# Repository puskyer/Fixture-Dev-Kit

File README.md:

# Fixture-Dev-Kit
A PCB for test fixture prototyping

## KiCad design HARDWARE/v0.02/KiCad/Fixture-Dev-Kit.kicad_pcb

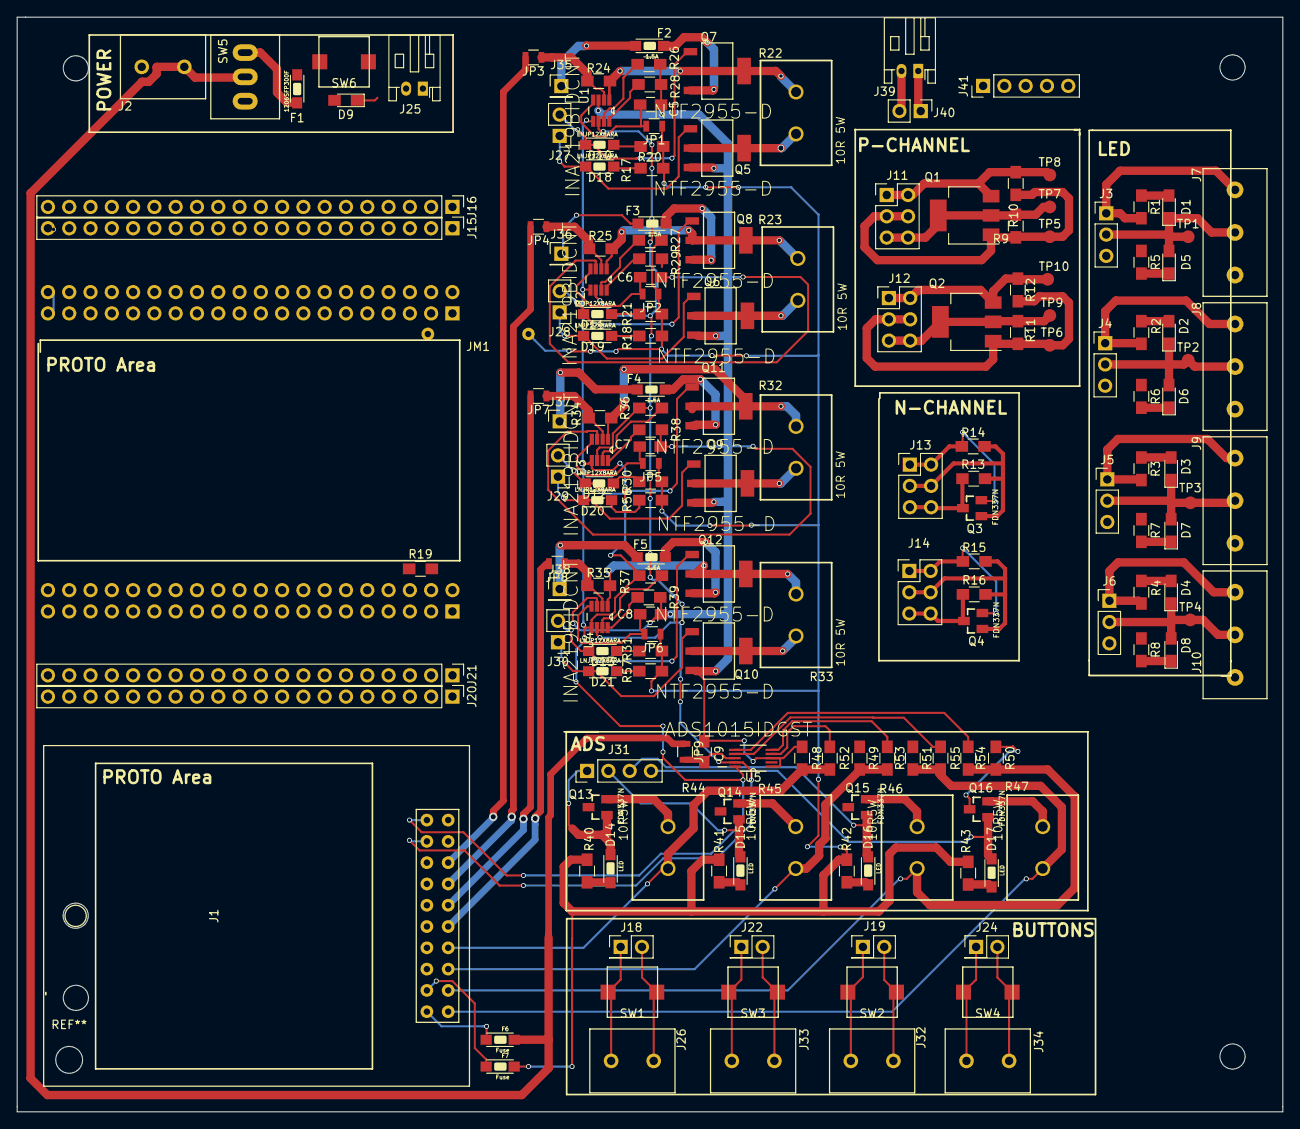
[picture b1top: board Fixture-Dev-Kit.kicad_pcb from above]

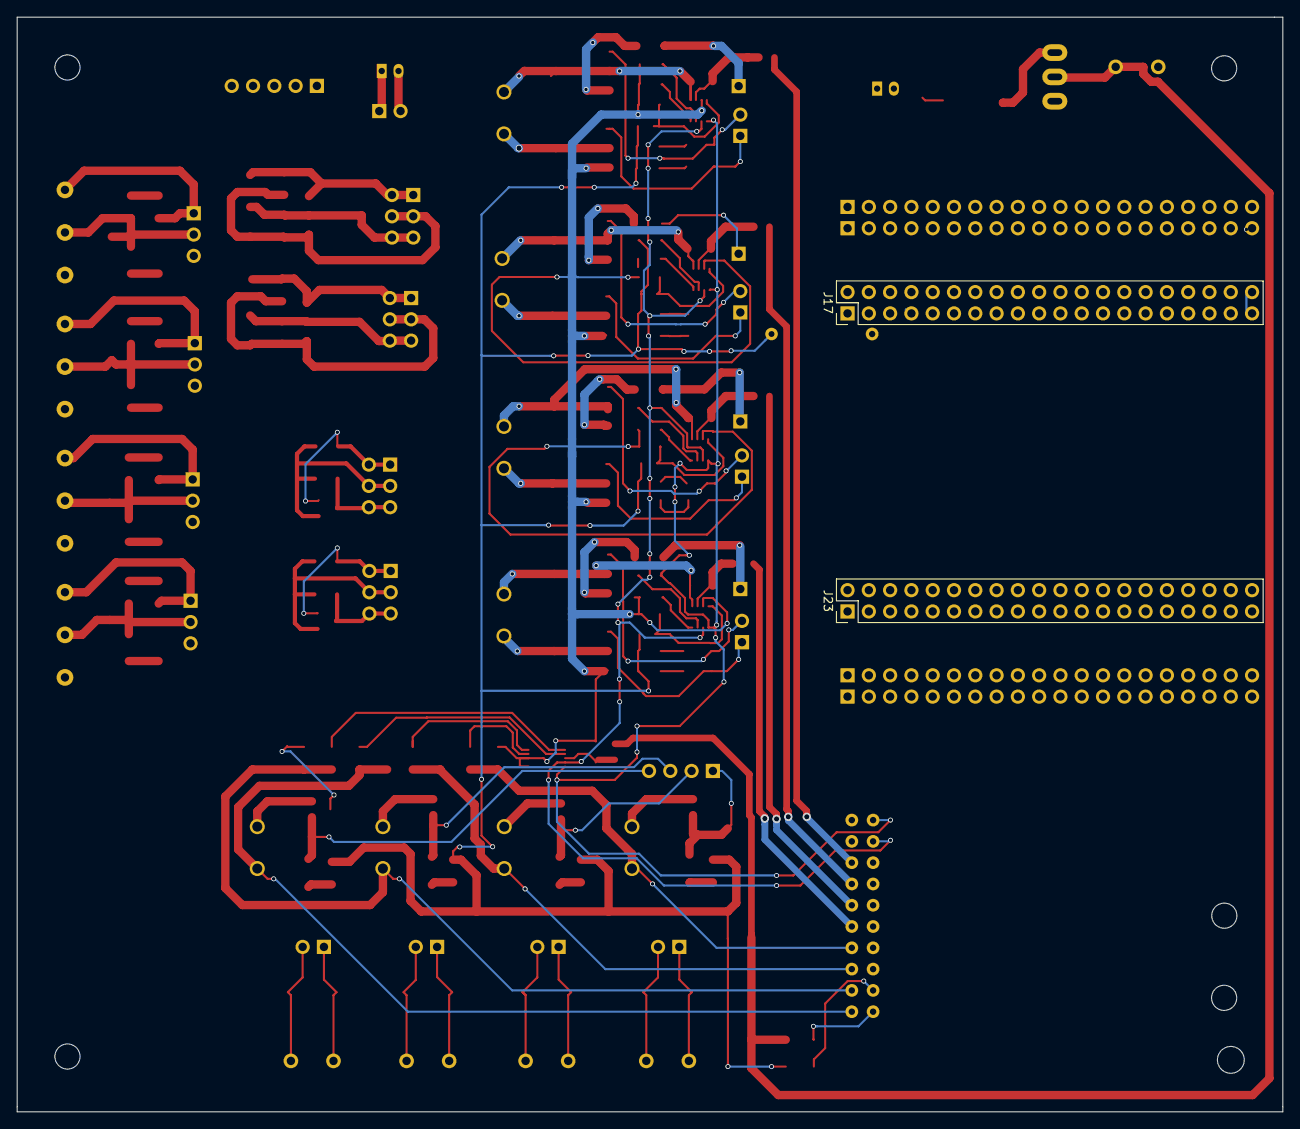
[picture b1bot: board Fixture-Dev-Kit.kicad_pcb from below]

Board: 2 copper layers, 151.0 x 130.6 mm, 178 parts (2 on the bottom side), 185 nets.

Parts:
C5, C6, C7, C8, C9: 0.1uF; C_0805_HandSoldering
D1, D2, D3, D4: Purple; LED_0805_HandSoldering
D5, D6, D7, D8: Green; LED_0805_HandSoldering
D9: LNJP12X8ARA; LED_0805_HandSoldering
D10, D11, D12, D13, D18, D19, D20, D21: LNJP12X8ARA; 1206
D14, D15, D16, D17: LED; 1206
F1: 1206SFP300F; 1206
F2, F3, F4, F5: 1.5A; 1206
F6, F7: Fuse; 1206
J1: DUT; DUT_HEADER_FOOTPRINT
J2: POWER; 2Pin5.08
J3: LED_0; Pin_Header_Straight_1x03_Pitch2.54mm
J4: LED_1; Pin_Header_Straight_1x03_Pitch2.54mm
J5: LED_2; Pin_Header_Straight_1x03_Pitch2.54mm
J6: LED_3; Pin_Header_Straight_1x03_Pitch2.54mm
J7: LED_0; 3Pin5.08
J8: LED_1; 3Pin5.08
J9: LED_2; 3Pin5.08
J10: LED_3; 3Pin5.08
J11, J12: FET_0; Pin_Header_Straight_2x03_Pitch2.54mm
J13: NFET_0; Pin_Header_Straight_2x03_Pitch2.54mm
J14: NFET_1; Pin_Header_Straight_2x03_Pitch2.54mm
J15, J16, J20, J21: Conn_01x20; Pin_Header_Straight_1x20_Pitch2.54mm
J17: CHIP4RH; Pin_Header_Straight_2x20_Pitch2.54mm
J18, J19, J22, J24: SW_0; Pin_Header_Straight_2x01_Pitch2.54mm
J23: CHIP4LH; Pin_Header_Straight_2x20_Pitch2.54mm
J25: JST-2P-RA; JST_PH_S2B-PH-K_02x2.00mm_Angled
J26, J32, J33, J34: SW_0; 2Pin5.08
J27, J28, J29, J30: INA_40; Pin_Header_Straight_1x02_Pitch2.54mm
J31: ADS; Pin_Header_Straight_1x04_Pitch2.54mm
J35: 40 V+; Pin_Header_Straight_1x01_Pitch2.54mm
J36: 41 V+; Pin_Header_Straight_1x01_Pitch2.54mm
J37: 42 V+; Pin_Header_Straight_1x01_Pitch2.54mm
J38: 43 V+; Pin_Header_Straight_1x01_Pitch2.54mm
J39: DUT BAT; JST_PH_S2B-PH-K_02x2.00mm_Angled
J40: DUT BAT; Pin_Header_Straight_1x02_Pitch2.54mm
J41: Conn_01x05; Pin_Header_Straight_1x05_Pitch2.54mm
JM1: JUMPER; Jumper
JP1, JP2, JP3, JP4, JP5, JP6, JP7, JP8, JP9: Jumper_NC_Small; R_0805
Q1, Q2: NTF2955T1G; SOT-223
Q3, Q4, Q13, Q14, Q15, Q16: FDN337N; SSOT-3
Q5, Q6, Q7, Q8, Q9, Q10, Q11, Q12: NTF2955-D; SOT230P700X180-4N
R1, R2, R3, R4, R5, R6, R7, R8, R26, R27, R28, R29, R36, R37, R38, R39: 1K; R_0805_HandSoldering
R9, R10, R11, R12, R13, R14, R15, R16: DNP; R_0805_HandSoldering
R17, R18, R20, R21, R30, R31, R40, R41, R42, R43, R56, R57: 160R; R_0805_HandSoldering
R19: 10K; R_0805_HandSoldering
R22, R23, R32, R33: 10R 5W; RES_TWM3J560E
R24, R25, R34, R35: 0.1R; R_0805_HandSoldering
R44, R45, R46, R47: 10R5W; RES_TWM3J560E
R48, R49, R50, R51: NC; R_0805_HandSoldering
R52: 0R; R_0805_HandSoldering
R53, R54, R55: 1R; R_0805_HandSoldering
SW1, SW2, SW3, SW4, SW6: TL9210AF260Q
SW5: YSS-19-1202-N
TP1, TP2, TP3, TP4: SIG; TestPoint
TP5: G0; TestPoint
TP6: G1; TestPoint
TP7, TP8, TP9, TP10: TEST; TestPoint
U1, U2, U3, U4: INA219BIDCNT; SOT65P280X145-8N
U5: ADS1015IDGST; SOP50P490X110-10N

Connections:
+5V: F6.1, J2.2, J41.1, J41.2, J41.3, J41.4, J41.5, JP9.1, SW5.2
/ADAPTER_ID: J1.16, J21.17, J23.34
/AIN0: J1.7, R44.2, R48.2, R52.1
/AIN1: J1.5, R45.2, R49.2, R53.1
/AIN2: J1.3, R46.2, R50.2, R54.1
/AIN3: J1.1, R47.2, R51.2, R55.1
/C4-VCC-3V3: F7.1, JM1.1, JP1.1, JP2.1, JP5.1, JP6.1, R17.2, R18.2, R20.2, R21.2, R27.2, R30.2, R31.2, R40.2, R41.2, R42.2, R43.2, R56.2, R57.2
/Fixture Dev Kit - ADS/AIN0_XIO: D14.1, J31.1, Q13.1
/Fixture Dev Kit - ADS/AIN1_XIO: D15.1, J31.2, Q14.1
/Fixture Dev Kit - ADS/AIN2_XIO: D16.1, J31.3, Q15.1
/Fixture Dev Kit - ADS/AIN3_XIO: D17.1, J31.4, Q16.1
/Fixture Dev Kit - Functional Computer/BAT: J21.4, J23.8, J25.2
/Fixture Dev Kit - Functional Computer/C4-PWR-IN: F1.2, J21.1, J23.2
/Fixture Dev Kit - Functional Computer/I2C-SCK: J15.19, J17.37
/Fixture Dev Kit - Functional Computer/I2C-SDA: J15.18, J17.35
/Fixture Dev Kit - Functional Computer/LOLN: J16.3, J17.6
/Fixture Dev Kit - Functional Computer/LOLP: J16.2, J17.4
/Fixture Dev Kit - Functional Computer/LORN: J16.5, J17.10
/Fixture Dev Kit - Functional Computer/LORP: J16.4, J17.8
/Fixture Dev Kit - Functional Computer/PWRON: J21.5, J23.10, SW6.1
/Fixture Dev Kit - Functional Computer/STATUSLED: D9.2, J15.5, J17.9, JM1.2
/Fixture Dev Kit - Functional Computer/TS: J21.3, J23.6, R19.1
/Fixture Dev Kit - INA/INA40_XIO: D10.1, J27.2, Q7.1
/Fixture Dev Kit - INA/INA41_XIO: D11.1, J28.2, Q8.1
/Fixture Dev Kit - INA/INA42_XIO: D12.1, J29.2, Q11.1
/Fixture Dev Kit - INA/INA43_XIO: D13.1, J30.2, Q12.1
/Fixture Dev Kit - INA/LOAD40_XIO: D18.1, J27.1, Q5.1
/Fixture Dev Kit - INA/LOAD41_XIO: D19.1, J28.1, Q6.1
/Fixture Dev Kit - INA/LOAD42_XIO: D20.1, J29.1, Q9.1
/Fixture Dev Kit - INA/LOAD43_XIO: D21.1, J30.1, Q10.1
/Fixture Dev Kit - PMosfets/Drain0: J11.5, J11.6, Q1.2, Q1.4, R9.2, TP7.1
/Fixture Dev Kit - PMosfets/Drain1: J12.5, J12.6, Q2.2, Q2.4, R11.2, TP9.1
/Fixture Dev Kit - PMosfets/Gate0: J11.3, J11.4, Q1.1, R9.1, R10.2, TP5.1
/Fixture Dev Kit - PMosfets/Gate1: J12.3, J12.4, Q2.1, R11.1, R12.2, TP6.1
/Fixture Dev Kit - PMosfets/Source0: J11.1, J11.2, Q1.3, R10.1, TP8.1
/Fixture Dev Kit - PMosfets/Source1: J12.1, J12.2, Q2.3, R12.1, TP10.1
/Fixture Dev Kits - NMosfets/Drain_0: J13.5, J13.6, Q3.3, R14.1
/Fixture Dev Kits - NMosfets/Drain_1: J14.5, J14.6, Q4.3, R16.1
/Fixture Dev Kits - NMosfets/Gate_0: J13.3, J13.4, Q3.1, R13.1, R14.2
/Fixture Dev Kits - NMosfets/Gate_1: J14.3, J14.4, Q4.1, R15.1, R16.2
/Fixture Dev Kits - NMosfets/Source_0: J13.1, J13.2, Q3.2, R13.2
/Fixture Dev Kits - NMosfets/Source_1: J14.1, J14.2, Q4.2, R15.2
/I2C-SCK: J1.20, R37.2, U1.5, U2.5, U3.5, U4.5, U5.10
/I2C-SDA: J1.18, R36.2, U1.6, U2.6, U3.6, U4.6, U5.9
/INA40_V-: J1.15, JP3.2
/INA41_V-: J1.13, JP4.2
/INA42_V-: J1.11, JP7.2
/INA43_V-: J1.9, JP8.2
/UART-RX: J1.17, J15.3, J17.5
/UART-TX: J1.19, J15.2, J17.3
GND: C5.1, C6.1, C7.1, C8.1, C9.2, D9.1, J1.6, J1.8, J1.10, J1.12, J1.14, J2.1, J3.3, J4.3, J5.3, J6.3, J7.3, J8.3, J9.3, J10.3, J15.1, J15.13, J15.20, J16.6, J16.20, J17.1, J17.25, J17.39, J17.40, J20.1, J20.7, J20.19, J20.20, J21.2, J21.6, J21.19, J21.20, J23.1, J23.4, J23.12, J23.13, J23.37, J23.38, J23.39, J23.40, J25.1, Q5.3, Q6.3, Q9.3, Q10.3, Q13.3, Q14.3, Q15.3, Q16.3, R5.1, R6.1, R7.1, R8.1, R19.2, R26.2, R28.2, R29.2, R38.2, R39.2, R48.1, R49.1, R50.1, R51.1, SW6.2, U1.3, U2.3, U3.3, U4.3, U5.1, U5.3
unnamed: C5.2, JP1.2, U1.4
unnamed: C6.2, JP2.2, U2.4
unnamed: C7.2, JP5.2, U3.4
unnamed: C8.2, JP6.2, U4.4
unnamed: C9.1, JP9.2, U5.8
unnamed: D1.1, D5.2, J3.2, J7.2, TP1.1
unnamed: D1.2, R1.1
unnamed: D2.1, D6.2, J4.2, J8.2, TP2.1
unnamed: D2.2, R2.1
unnamed: D3.1, D7.2, J5.2, J9.2, TP3.1
unnamed: D3.2, R3.1
unnamed: D4.1, D8.2, J6.2, J10.2, TP4.1
unnamed: D4.2, R4.1
unnamed: D5.1, R5.2
unnamed: D6.1, R6.2
unnamed: D7.1, R7.2
unnamed: D8.1, R8.2
unnamed: D10.2, R20.1
unnamed: D11.2, R21.1
unnamed: D12.2, R30.1
unnamed: D13.2, R31.1
unnamed: D14.2, R40.1
unnamed: D15.2, R41.1
unnamed: D16.2, R42.1
unnamed: D17.2, R43.1
unnamed: D18.2, R17.1
unnamed: D19.2, R18.1
unnamed: D20.2, R56.1
unnamed: D21.2, R57.1
unnamed: F1.1, SW5.3
unnamed: F2.1, Q7.3
unnamed: F2.2, J35.1
unnamed: F3.1, Q8.3
unnamed: F3.2, J36.1
unnamed: F4.1, Q11.3
unnamed: F4.2, J37.1
unnamed: F5.1, Q12.3
unnamed: F5.2, J38.1
unnamed: F6.2, J1.2
unnamed: F7.2, J1.4
unnamed: J3.1, J7.1, R1.2
unnamed: J4.1, J8.1, R2.2
unnamed: J5.1, J9.1, R3.2
unnamed: J6.1, J10.1, R4.2
unnamed: J15.4, J17.7
unnamed: J15.6, J17.11
unnamed: J15.7, J17.13
unnamed: J15.8, J17.15
unnamed: J15.9, J17.17
unnamed: J15.10, J17.19
unnamed: J15.11, J17.21
unnamed: J15.12, J17.23
unnamed: J15.14, J17.27
unnamed: J15.15, J17.29
unnamed: J15.16, J17.31
unnamed: J15.17, J17.33
unnamed: J16.1, J17.2
unnamed: J16.7, J17.14
unnamed: J16.8, J17.16
unnamed: J16.9, J17.18
unnamed: J16.10, J17.20
unnamed: J16.11, J17.22
unnamed: J16.12, J17.24
unnamed: J16.13, J17.26
unnamed: J16.14, J17.28
unnamed: J16.15, J17.30
unnamed: J16.16, J17.32
unnamed: J16.18, J17.34
unnamed: J16.19, J17.38
unnamed: J18.1, J26.1, SW1.1
unnamed: J18.2, J26.2, SW1.2
unnamed: J19.1, J32.1, SW2.1
unnamed: J19.2, J32.2, SW2.2
unnamed: J20.2, J23.3
unnamed: J20.3, J23.5
unnamed: J20.4, J23.7
unnamed: J20.5, J23.9
unnamed: J20.6, J23.11
unnamed: J20.8, J23.15
unnamed: J20.9, J23.17
unnamed: J20.10, J23.19
unnamed: J20.11, J23.21
unnamed: J20.12, J23.23
unnamed: J20.13, J23.25
unnamed: J20.14, J23.27
unnamed: J20.15, J23.29
unnamed: J20.16, J23.31
unnamed: J20.17, J23.33
unnamed: J20.18, J23.35
unnamed: J21.7, J23.14
unnamed: J21.8, J23.16
unnamed: J21.9, J23.18
unnamed: J21.10, J23.20
unnamed: J21.11, J23.22
unnamed: J21.12, J23.24
unnamed: J21.13, J23.26
unnamed: J21.14, J23.28
unnamed: J21.15, J23.30
unnamed: J21.16, J23.32
unnamed: J21.18, J23.36
unnamed: J22.1, J33.1, SW3.1
unnamed: J22.2, J33.2, SW3.2
unnamed: J24.1, J34.1, SW4.1
unnamed: J24.2, J34.2, SW4.2
unnamed: J39.1, J40.1
unnamed: J39.2, J40.2
unnamed: JP3.1, R24.2, U1.2
unnamed: JP4.1, R25.2, U2.2
unnamed: JP7.1, R34.2, U3.2
unnamed: JP8.1, R35.2, U4.2
unnamed: Q5.2, Q5.4, R22.1
unnamed: Q6.2, Q6.4, R23.1
unnamed: Q7.2, Q7.4, R22.2, R24.1, U1.1
unnamed: Q8.2, Q8.4, R23.2, R25.1, U2.1
unnamed: Q9.2, Q9.4, R32.1
unnamed: Q10.2, Q10.4, R33.1
unnamed: Q11.2, Q11.4, R32.2, R34.1, U3.1
unnamed: Q12.2, Q12.4, R33.2, R35.1, U4.1
unnamed: Q13.2, R44.1
unnamed: Q14.2, R45.1
unnamed: Q15.2, R46.1
unnamed: Q16.2, R47.1
unnamed: R26.1, U1.7
unnamed: R27.1, U2.7
unnamed: R28.1, U1.8
unnamed: R29.1, U2.8
unnamed: R36.1, U3.7
unnamed: R37.1, U4.7
unnamed: R38.1, U3.8
unnamed: R39.1, U4.8
unnamed: R52.2, U5.4
unnamed: R53.2, U5.5
unnamed: R54.2, U5.6
unnamed: R55.2, U5.7

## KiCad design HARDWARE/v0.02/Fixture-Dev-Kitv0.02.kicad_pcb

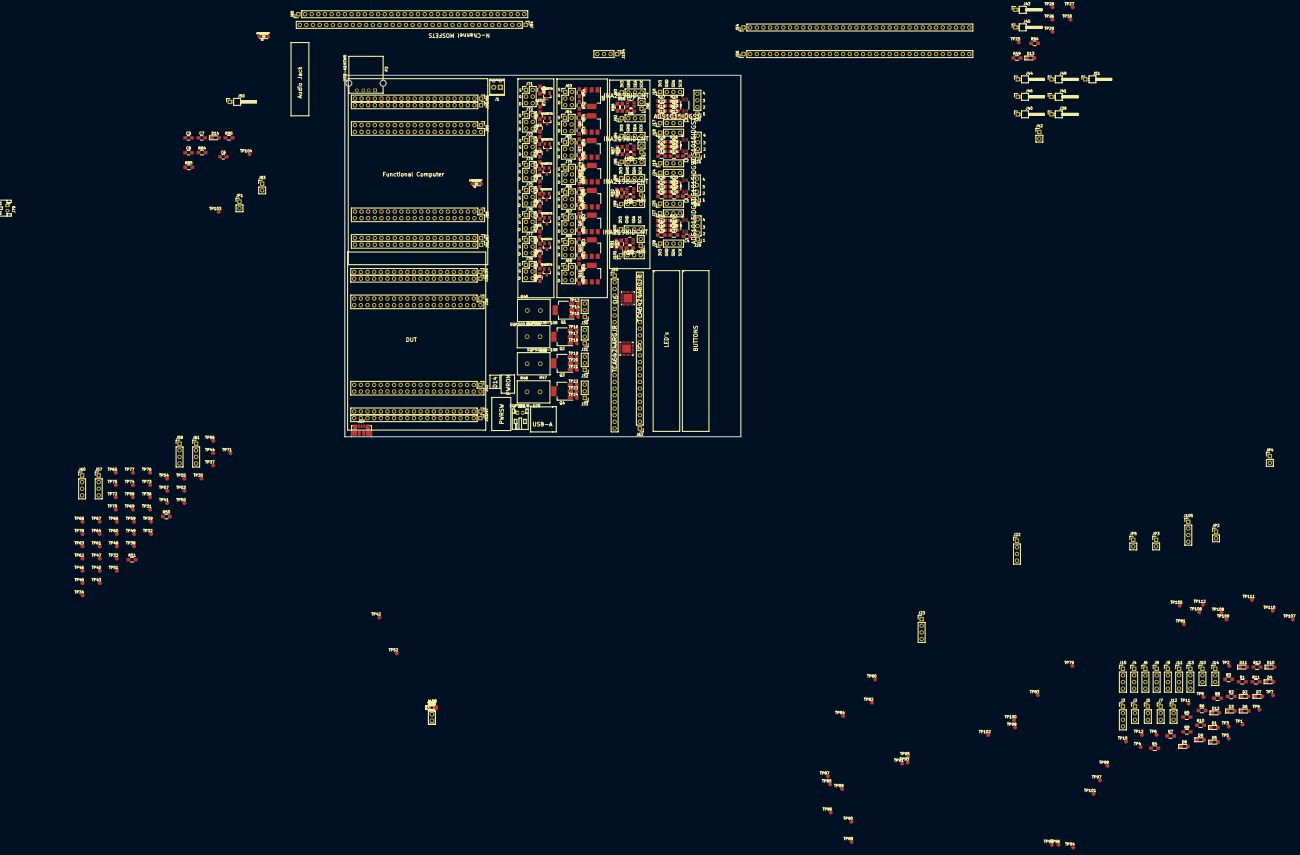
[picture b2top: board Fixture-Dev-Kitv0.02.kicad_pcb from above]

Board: 2 copper layers, 151.4 x 138.2 mm, 381 parts (0 on the bottom side), 343 nets, no tracks yet.

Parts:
C1, C2, C3, C4, C9, C10, C11, C12: 0.1uF; C_0805_HandSoldering
C5, C6, C7, C8: 1uf; C_0805_HandSoldering
D1, D3, D5, D7, D9, D11, D15, D17: Purple; LED_0805_HandSoldering
D2, D4, D6, D8, D10, D12, D16, D18: Green; LED_0805_HandSoldering
D13, D14: LNJP12X8ARA; LED_0805_HandSoldering
F1, F2: 1206SFP300F; 1206
J1: POWER; TerminalBlock_Phoenix_MPT-2.54mm_2pol
J2: LED_0; Pin_Header_Straight_1x03_Pitch2.54mm
J3: SW_0; Pin_Header_Straight_1x04_Pitch2.54mm
J4: SW_1; Pin_Header_Straight_1x04_Pitch2.54mm
J5: LED_1; Pin_Header_Straight_1x03_Pitch2.54mm
J6: SW_2; Pin_Header_Straight_1x04_Pitch2.54mm
J7: LED_2; Pin_Header_Straight_1x03_Pitch2.54mm
J8: SW_3; Pin_Header_Straight_1x04_Pitch2.54mm
J9: SW_4; Pin_Header_Straight_1x04_Pitch2.54mm
J10: LED_3; Pin_Header_Straight_1x03_Pitch2.54mm
J11: SW_5; Pin_Header_Straight_1x04_Pitch2.54mm
J12: LED_4; Pin_Header_Straight_1x03_Pitch2.54mm
J13: SW_6; Pin_Header_Straight_1x04_Pitch2.54mm
J14: LED_5; Pin_Header_Straight_1x03_Pitch2.54mm
J15: SW_7; Pin_Header_Straight_1x04_Pitch2.54mm
J16, J17, J20: ADS_48; Pin_Header_Straight_1x04_Pitch2.54mm
J18, J19, J21: ADS_4A; Pin_Header_Straight_1x04_Pitch2.54mm
J22, J23: ADS; Pin_Header_Straight_1x04_Pitch2.54mm
J24, J25, J26: ADS_49; Pin_Header_Straight_1x04_Pitch2.54mm
J27, J28, J29: ADS_4B; Pin_Header_Straight_1x04_Pitch2.54mm
J30: LOAD_0; Pin_Header_Straight_1x03_Pitch2.54mm
J31: LOAD_1; Pin_Header_Straight_1x03_Pitch2.54mm
J32: LOAD_2; Pin_Header_Straight_1x03_Pitch2.54mm
J33: LOAD_3; Pin_Header_Straight_1x03_Pitch2.54mm
J34, J38, J47, J53, J86, J87, J90, J91: Conn_01x20; Pin_Header_Straight_1x20_Pitch2.54mm
J35: BAT; JST_PH_S2B-PH-K_02x2.00mm_Angled
J36, J88: CHIP4LH; Pin_Header_Straight_2x20_Pitch2.54mm
J37: USB_OTG; USB_Micro-B_Molex_47346-0001
J39, J40, J49: VBUS; Pin_Header_Angled_1x01_Pitch2.54mm
J41: B_D+; Pin_Header_Angled_1x01_Pitch2.54mm
J42: D-TP's; Pin_Header_Straight_1x02_Pitch2.54mm
J43: B_D-; Pin_Header_Angled_1x01_Pitch2.54mm
J44: USB_ID; Pin_Header_Angled_1x01_Pitch2.54mm
J45: UPDATE; Pin_Header_Angled_1x01_Pitch2.54mm
J46: ANT--SELECT; Pin_Header_Angled_1x01_Pitch2.54mm
J50: A_D+; Pin_Header_Angled_1x01_Pitch2.54mm
J51: A_D-; Pin_Header_Angled_1x01_Pitch2.54mm
J52, J89: CHIP4RH; Pin_Header_Straight_2x20_Pitch2.54mm
J54, J56, J80, J84: Conn_01x35; Pin_Header_Straight_1x35_Pitch2.54mm
J57, J58, J60, J61: IOExp_0; Pin_Header_Straight_1x04_Pitch2.54mm
J59, J62: Conn_01x24; Pin_Header_Straight_1x24_Pitch2.54mm
J63, J64, J65, J66, J67, J68, J69, J70: FET_0; Pin_Header_Straight_2x03_Pitch2.54mm
J71: NFET_0; Pin_Header_Straight_2x03_Pitch2.54mm
J72: NFET_4; Pin_Header_Straight_2x03_Pitch2.54mm
J73: NFET_1; Pin_Header_Straight_2x03_Pitch2.54mm
J74: NFET_5; Pin_Header_Straight_2x03_Pitch2.54mm
J75: NFET_2; Pin_Header_Straight_2x03_Pitch2.54mm
J76: NFET_6; Pin_Header_Straight_2x03_Pitch2.54mm
J77: NFET_3; Pin_Header_Straight_2x03_Pitch2.54mm
J78: NFET_7; Pin_Header_Straight_2x03_Pitch2.54mm
J79: JST-2P-RA; JST_PH_S2B-PH-K_02x2.00mm_Angled
J83: VBUS; Pin_Header_Straight_1x02_Pitch2.54mm
J92, J93: INA_40; Pin_Header_Straight_1x04_Pitch2.54mm
J94, J95: INA_42; Pin_Header_Straight_1x04_Pitch2.54mm
J96: INA_40; Pin_Header_Straight_1x02_Pitch2.54mm
J97: INA_42; Pin_Header_Straight_1x02_Pitch2.54mm
J98, J99: INA_41; Pin_Header_Straight_1x04_Pitch2.54mm
J100, J101: INA_43; Pin_Header_Straight_1x04_Pitch2.54mm
J102: INA_41; Pin_Header_Straight_1x02_Pitch2.54mm
J103: INA_43; Pin_Header_Straight_1x02_Pitch2.54mm
J104, J105: INA; Pin_Header_Straight_1x04_Pitch2.54mm
J106: LED_6; Pin_Header_Straight_1x03_Pitch2.54mm
J107: LED_7; Pin_Header_Straight_1x03_Pitch2.54mm
JP1: Jumper_NC; Pin_Header_Straight_1x02_Pitch2.54mm
JP2, JP3, JP4, JP5: Jumper_NO; Pin_Header_Straight_1x02_Pitch2.54mm
P2: USB-A1HSW6; OST_USB-A1HSW6
Q1, Q2, Q3, Q4, Q5, Q6, Q7, Q8, Q9, Q10, Q11, Q12: NTF2955T1G; SOT-223
Q13, Q14, Q15, Q16, Q17, Q18, Q19, Q20: FDN337N; SSOT-3
R1, R2, R3, R4, R5, R6, R7, R8, R9, R10, R11, R12, R13, R14, R15, R16, R17, R18, R19, R20, R21, R22, R23, R24, R25, R26, R27, R28, R29, R30, R31, R32, R33, R34, R35, R36, R37, R38, R39, R40, R41, R42, R43, R44, R50, R51, R86, R87, R88, R89, R90, R91, R92, R93, R96, R97, R98, R99: 1K; R_0805_HandSoldering
R45, R46, R47, R48: SQP500JB-10R; RES_TWM3J560E
R49, R95: 10K; R_0805_HandSoldering
R52, R53, R54, R55, R56, R57, R58, R59, R60, R61, R62, R63, R64, R65, R66, R67, R68, R69, R70, R71, R72, R73, R74, R75, R76, R77, R78, R79, R80, R81, R82, R83: DNP; R_0805_HandSoldering
R84, R85: 0R; R_0805_HandSoldering
R94: 47K; R_0805_HandSoldering
TP1, TP2, TP3, TP4, TP5, TP6, TP7, TP8, TP10, TP12: SIG; TestPoint
TP9, TP11: VS; TestPoint
TP13, TP16, TP19, TP22: S; TestPoint
TP14, TP17, TP20, TP23: G; TestPoint
TP15, TP18, TP21, TP24: D; TestPoint
TP25: VBUS; TestPoint
TP26: B_D+; TestPoint
TP27: B_D-; TestPoint
TP28: USB-ID; TestPoint
TP29: A_D+; TestPoint
TP30: A_D-; TestPoint
TP31, TP32, TP33, TP34, TP35, TP36, TP37, TP38, TP39, TP40, TP41, TP42, TP43, TP44, TP45, TP46, TP47, TP48, TP49, TP50, TP51, TP52, TP53, TP54, TP55, TP56, TP57, TP58, TP59, TP60, TP61, TP62, TP63, TP64, TP65, TP66, TP67, TP68, TP69, TP70, TP71, TP72, TP73, TP74, TP75, TP76, TP77, TP78, TP79, TP80, TP83, TP84, TP85, TP86, TP89, TP90, TP91, TP92, TP95, TP96, TP97, TP98, TP101, TP102: TEST; TestPoint
TP81: G0; TestPoint
TP82, TP99: G3; TestPoint
TP87: G1; TestPoint
TP88: G4; TestPoint
TP93: G2; TestPoint
TP94: G5; TestPoint
TP100: G6; TestPoint
TP103: D-; TestPoint
TP104: D+; TestPoint
TP105, TP107, TP109, TP111: V+; TestPoint
TP106, TP108, TP110, TP112: V-; TestPoint
U1, U2, U3, U4: ADS1015IDGST; SOP50P490X110-10N
U5, U6: TCA6424ARGJR; QFN50P500X500X60-33N
U7, U8, U9, U10: INA219BIDCNT; SOT65P280X145-8N

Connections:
/Fixture Dev Kit - ADS/C4-VCC-3V3: C1.1, C2.1, C3.1, C4.1, D14.2, J16.1, J17.1, J18.1, J19.1, J22.4, J23.4, J24.1, J25.1, J27.1, J28.1, J57.4, J58.4, J60.4, J61.4, J86.5, J89.9, J92.1, J93.1, J94.1, J95.1, J98.1, J99.1, J100.1, J101.1, J104.4, J105.4, JP2.1, JP3.1, JP4.1, JP5.1, R50.2, R51.2, R92.2, U1.8, U2.8, U3.1, U3.8, U4.8, U5.27, U5.31, U6.26, U6.27, U6.31
/Fixture Dev Kit - ADS/I2C-SCK: J16.4, J17.4, J18.4, J19.4, J22.1, J23.1, J24.4, J25.4, J27.4, J28.4, U1.10, U2.10, U3.10, U4.1, U4.10
/Fixture Dev Kit - ADS/I2C-SDA: J16.3, J17.3, J18.3, J19.3, J22.2, J23.2, J24.3, J25.3, J27.3, J28.3, U1.9, U2.1, U2.9, U3.9, U4.9
/Fixture Dev Kit - DUT/D-BAT: J35.1, J36.8, J38.4, J56.1, J56.2, J56.3, J56.4, J56.5
/Fixture Dev Kit - DUT/D-PWRON_SW: J36.10, J38.5, J54.5
/Fixture Dev Kit - DUT/D-STATUS_LED: J47.5, J52.9, R94.1
/Fixture Dev Kit - DUT/D-TS: J36.6, J38.3, J56.6, R49.1
/Fixture Dev Kit - DUT/DUT-CHG-IN: F2.2, J36.2, J38.1, J56.31, J56.32, J56.33, J56.34, J56.35
/Fixture Dev Kit - Functional Computer/BAT: J79.2, J80.1, J80.2, J80.3, J80.4, J80.5, J88.8, J91.4
/Fixture Dev Kit - Functional Computer/C4-PWR-IN: F1.2, J80.31, J80.32, J80.33, J80.34, J80.35, J88.2, J91.1
/Fixture Dev Kit - Functional Computer/C4-VCC-5V: J89.2, J90.1
/Fixture Dev Kit - Functional Computer/I2C-SCK: J57.1, J58.1, J60.1, J61.1, J80.30, J86.19, J89.37, J92.4, J93.4, J94.4, J95.4, J98.4, J99.4, J100.4, J101.4, J104.1, J105.1, R93.2, U5.29, U6.29, U7.5, U8.5, U9.5, U10.5
/Fixture Dev Kit - Functional Computer/I2C-SDA: J57.2, J58.2, J60.2, J61.2, J80.29, J86.18, J89.35, J92.3, J93.3, J94.3, J95.3, J98.3, J99.3, J100.3, J101.3, J104.2, J105.2, R89.2, U5.30, U6.30, U7.6, U8.6, U9.6, U10.6
/Fixture Dev Kit - Functional Computer/LOLN: C7.1, J84.6, J89.6, J90.3
/Fixture Dev Kit - Functional Computer/LOLP: J84.7, J89.4, J90.2, R85.1
/Fixture Dev Kit - Functional Computer/LORN: C8.1, J84.9, J89.10, J90.5
/Fixture Dev Kit - Functional Computer/LORP: J84.8, J89.8, J90.4, R84.1
/Fixture Dev Kit - Functional Computer/PWRON: J84.5, J88.10, J91.5
/Fixture Dev Kit - Functional Computer/TS: J80.6, J88.6, J91.3, R95.1
/Fixture Dev Kit - Functional Computer/USBOTG_B_DM: J84.27, P2.2, TP103.1
/Fixture Dev Kit - Functional Computer/USBOTG_B_DP: J84.26, P2.3, TP104.1
/Fixture Dev Kit - Functional Computer/USBOTG_B_ID: J84.28, JP1.1
/Fixture Dev Kit - PMosfets/Drain0: J63.5, J63.6, Q5.2, Q5.4, R52.2, TP79.1
/Fixture Dev Kit - PMosfets/Drain1: J65.5, J65.6, Q7.2, Q7.4, R56.2, TP85.1
/Fixture Dev Kit - PMosfets/Drain2: J67.5, J67.6, Q9.2, Q9.4, R60.2, TP91.1
/Fixture Dev Kit - PMosfets/Drain3: J69.5, J69.6, Q11.2, Q11.4, R64.2, TP97.1
/Fixture Dev Kit - PMosfets/Drain4: J64.5, J64.6, Q6.2, Q6.4, R53.2, TP80.1
/Fixture Dev Kit - PMosfets/Drain5: J66.5, J66.6, Q8.2, Q8.4, R57.2, TP86.1
/Fixture Dev Kit - PMosfets/Drain6: J68.5, J68.6, Q10.2, Q10.4, R61.2, TP92.1
/Fixture Dev Kit - PMosfets/Drain7: J70.5, J70.6, Q12.2, Q12.4, R65.2, TP98.1
/Fixture Dev Kit - PMosfets/Gate0: J63.3, J63.4, Q5.1, R52.1, R54.2, TP81.1
/Fixture Dev Kit - PMosfets/Gate1: J65.3, J65.4, Q7.1, R56.1, R58.2, TP87.1
/Fixture Dev Kit - PMosfets/Gate2: J67.3, J67.4, Q9.1, R60.1, R62.2, TP93.1
/Fixture Dev Kit - PMosfets/Gate3: J69.3, J69.4, Q11.1, R64.1, R66.2, TP99.1
/Fixture Dev Kit - PMosfets/Gate4: J64.3, J64.4, Q6.1, R53.1, R55.2, TP82.1
/Fixture Dev Kit - PMosfets/Gate5: J66.3, J66.4, Q8.1, R57.1, R59.2, TP88.1
/Fixture Dev Kit - PMosfets/Gate6: J68.3, J68.4, Q10.1, R61.1, R63.2, TP94.1
/Fixture Dev Kit - PMosfets/Gate7: J70.3, J70.4, Q12.1, R65.1, R67.2, TP100.1
/Fixture Dev Kit - PMosfets/Source0: J63.1, J63.2, Q5.3, R54.1, TP83.1
/Fixture Dev Kit - PMosfets/Source1: J65.1, J65.2, Q7.3, R58.1, TP89.1
/Fixture Dev Kit - PMosfets/Source2: J67.1, J67.2, Q9.3, R62.1, TP95.1
/Fixture Dev Kit - PMosfets/Source3: J69.1, J69.2, Q11.3, R66.1, TP101.1
/Fixture Dev Kit - PMosfets/Source4: J64.1, J64.2, Q6.3, R55.1, TP84.1
/Fixture Dev Kit - PMosfets/Source5: J66.1, J66.2, Q8.3, R59.1, TP90.1
/Fixture Dev Kit - PMosfets/Source6: J68.1, J68.2, Q10.3, R63.1, TP96.1
/Fixture Dev Kit - PMosfets/Source7: J70.1, J70.2, Q12.3, R67.1, TP102.1
/Fixture Dev Kits - NMosfets/Drain_0: J71.5, J71.6, Q13.3, R70.1
/Fixture Dev Kits - NMosfets/Drain_1: J73.5, J73.6, Q15.3, R74.1
/Fixture Dev Kits - NMosfets/Drain_2: J75.1, J75.2, J75.5, J75.6, Q17.2, Q17.3, R76.2, R78.1
/Fixture Dev Kits - NMosfets/Drain_3: J77.1, J77.2, J77.5, J77.6, Q19.2, Q19.3, R80.2, R82.1
/Fixture Dev Kits - NMosfets/Drain_4: J72.1, J72.2, J72.5, J72.6, Q14.2, Q14.3, R69.2, R71.1
/Fixture Dev Kits - NMosfets/Drain_5: J74.1, J74.2, J74.5, J74.6, Q16.2, Q16.3, R73.2, R75.1
/Fixture Dev Kits - NMosfets/Drain_6: J76.1, J76.2, J76.5, J76.6, Q18.2, Q18.3, R77.2, R79.1
/Fixture Dev Kits - NMosfets/Drain_7: J78.1, J78.2, J78.5, J78.6, Q20.2, Q20.3, R81.2, R83.1
/Fixture Dev Kits - NMosfets/Gate_0: J71.3, J71.4, Q13.1, R68.1, R70.2
/Fixture Dev Kits - NMosfets/Gate_1: J73.3, J73.4, Q15.1, R72.1, R74.2
/Fixture Dev Kits - NMosfets/Gate_2: J75.3, J75.4, Q17.1, R76.1, R78.2
/Fixture Dev Kits - NMosfets/Gate_3: J77.3, J77.4, Q19.1, R80.1, R82.2
/Fixture Dev Kits - NMosfets/Gate_4: J72.3, J72.4, Q14.1, R69.1, R71.2
/Fixture Dev Kits - NMosfets/Gate_5: J74.3, J74.4, Q16.1, R73.1, R75.2
/Fixture Dev Kits - NMosfets/Gate_6: J76.3, J76.4, Q18.1, R77.1, R79.2
/Fixture Dev Kits - NMosfets/Gate_7: J78.3, J78.4, Q20.1, R81.1, R83.2
/Fixture Dev Kits - NMosfets/Source_0: J71.1, J71.2, Q13.2, R68.2
/Fixture Dev Kits - NMosfets/Source_1: J73.1, J73.2, Q15.2, R72.2
GND: C1.2, C2.2, C3.2, C4.2, C7.2, C8.2, C9.1, C10.1, C11.1, C12.1, D13.1, D14.1, J1.1, J2.3, J5.3, J7.3, J10.3, J12.3, J14.3, J16.2, J17.2, J18.2, J19.2, J22.3, J23.3, J24.2, J25.2, J27.2, J28.2, J34.1, J34.19, J34.20, J35.2, J36.1, J36.4, J36.12, J36.37, J36.38, J36.39, J36.40, J37.5, J37.6, J38.2, J38.6, J38.19, J38.20, J47.1, J47.13, J47.20, J52.1, J52.25, J52.39, J52.40, J53.6, J53.20, J54.1, J54.2, J54.3, J54.4, J54.31, J54.32, J54.33, J54.34, J54.35, J57.3, J58.3, J60.3, J61.3, J79.1, J84.1, J84.2, J84.3, J84.4, J84.31, J84.32, J84.33, J84.34, J84.35, J86.1, J86.13, J86.20, J87.1, J87.7, J87.19, J87.20, J88.1, J88.4, J88.12, J88.13, J88.37, J88.38, J88.39, J88.40, J89.1, J89.25, J89.39, J89.40, J90.6, J90.20, J91.2, J91.6, J91.19, J91.20, J92.2, J93.2, J94.2, J95.2, J98.2, J99.2, J100.2, J101.2, J104.3, J105.3, J106.3, J107.3, JP1.2, P2.4, R2.1, R4.1, R6.1, R8.1, R10.1, R12.1, R15.1, R16.1, R19.1, R20.1, R23.1, R24.1, R27.1, R28.1, R30.1, R32.1, R34.1, R36.1, R38.1, R40.1, R42.1, R44.1, R49.2, R86.2, R87.2, R88.2, R90.2, R91.2, R95.2, R97.1, R99.1, U1.1, U1.3, U2.3, U3.3, U4.3, U5.25, U5.26, U5.33, U6.25, U6.33, U7.3, U8.3, U9.3, U10.3
unnamed: C5.1, R84.2
unnamed: C6.1, R85.2
unnamed: C9.2, JP2.2, U7.4
unnamed: C10.2, JP3.2, U8.4
unnamed: C11.2, JP4.2, U9.4
unnamed: C12.2, JP5.2, U10.4
unnamed: D1.1, D2.2, J2.2, TP1.1
unnamed: D1.2, R1.1
unnamed: D2.1, R2.2
unnamed: D3.1, D4.2, J5.2, TP2.1
unnamed: D3.2, R3.1
unnamed: D4.1, R4.2
unnamed: D5.1, D6.2, J7.2, TP3.1
unnamed: D5.2, R5.1
unnamed: D6.1, R6.2
unnamed: D7.1, D8.2, J10.2, TP4.1
unnamed: D7.2, R7.1
unnamed: D8.1, R8.2
unnamed: D9.2, R9.1
unnamed: D10.1, R10.2, TP9.1
unnamed: D9.1, D10.2, J12.2, TP5.1, TP10.1
unnamed: D11.1, D12.2, J14.2, TP6.1, TP12.1
unnamed: D11.2, R11.1, TP11.1
unnamed: D12.1, R12.2
unnamed: D13.2, R94.2
unnamed: D15.1, D16.2, J106.2, TP7.1
unnamed: D15.2, R96.1
unnamed: D16.1, R97.2
unnamed: D17.1, D18.2, J107.2, TP8.1
unnamed: D17.2, R98.1
unnamed: D18.1, R99.2
unnamed: J2.1, R1.2
unnamed: J5.1, R3.2
unnamed: J7.1, R5.2
unnamed: J10.1, R7.2
unnamed: J12.1, R9.2
unnamed: J14.1, R11.2
unnamed: J20.1, R13.1, R15.2
unnamed: J20.2, R17.1, R19.2
unnamed: J20.3, R21.1, R23.2
unnamed: J20.4, R25.1, R27.2
unnamed: J21.1, R14.1, R16.2
unnamed: J21.2, R18.1, R20.2
unnamed: J21.3, R22.1, R24.2
unnamed: J21.4, R26.1, R28.2
unnamed: J26.1, R29.1, R30.2
unnamed: J26.2, R31.1, R32.2
unnamed: J26.3, R33.1, R34.2
unnamed: J26.4, R35.1, R36.2
unnamed: J29.1, R37.1, R38.2
unnamed: J29.2, R39.1, R40.2
unnamed: J29.3, R41.1, R42.2
unnamed: J29.4, R43.1, R44.2
unnamed: J30.1, R45.2, TP15.1
unnamed: J30.2, Q1.1, TP14.1
unnamed: J30.3, Q1.3, TP13.1
unnamed: J31.1, R46.2, TP18.1
unnamed: J31.2, Q2.1, TP17.1
unnamed: J31.3, Q2.3, TP16.1
unnamed: J32.1, R47.2, TP21.1
unnamed: J32.2, Q3.1, TP20.1
unnamed: J32.3, Q3.3, TP19.1
unnamed: J33.1, R48.2, TP24.1
unnamed: J33.2, Q4.1, TP23.1
unnamed: J33.3, Q4.3, TP22.1
unnamed: J34.2, J36.3
unnamed: J34.3, J36.5
unnamed: J34.4, J36.7
unnamed: J34.5, J36.9
unnamed: J34.6, J36.11
unnamed: J34.7, J36.13
unnamed: J34.8, J36.15
unnamed: J34.9, J36.17
unnamed: J34.10, J36.19
unnamed: J34.11, J36.21
unnamed: J34.12, J36.23
unnamed: J34.13, J36.25
unnamed: J34.14, J36.27
unnamed: J34.15, J36.29
unnamed: J34.16, J36.31
unnamed: J34.17, J36.33
unnamed: J34.18, J36.35
unnamed: J36.14, J38.7
unnamed: J36.16, J38.8
unnamed: J36.18, J38.9
unnamed: J36.20, J38.10
unnamed: J36.22, J38.11
unnamed: J36.24, J38.12
unnamed: J36.26, J38.13
unnamed: J36.28, J38.14
unnamed: J36.30, J38.15
unnamed: J36.32, J38.16
unnamed: J36.34, J38.17
unnamed: J36.36, J38.18
unnamed: J37.1, J39.1, J40.1, TP25.1
unnamed: J37.2, J41.1, TP27.1
unnamed: J37.3, J43.1, TP26.1
unnamed: J37.4, J44.1, TP28.1
unnamed: J42.1, J46.1
unnamed: J42.2, J45.1
unnamed: J47.2, J52.3
unnamed: J47.3, J52.5
unnamed: J47.4, J52.7
unnamed: J47.6, J52.11
unnamed: J47.7, J52.13
unnamed: J47.8, J52.15
unnamed: J47.9, J52.17
unnamed: J47.10, J52.19
unnamed: J47.11, J52.21
unnamed: J47.12, J52.23
unnamed: J47.14, J52.27
unnamed: J47.15, J52.29
unnamed: J47.16, J52.31
unnamed: J47.17, J52.33
unnamed: J47.18, J52.35
unnamed: J47.19, J52.37
unnamed: J50.1, TP29.1
unnamed: J51.1, TP30.1
unnamed: J52.2, J53.1
unnamed: J52.4, J53.2
unnamed: J52.6, J53.3
unnamed: J52.8, J53.4
unnamed: J52.10, J53.5
unnamed: J52.14, J53.7
unnamed: J52.16, J53.8
unnamed: J52.18, J53.9
unnamed: J52.20, J53.10
unnamed: J52.22, J53.11
unnamed: J52.24, J53.12
unnamed: J52.26, J53.13
unnamed: J52.28, J53.14
unnamed: J52.30, J53.15
unnamed: J52.32, J53.16
unnamed: J52.34, J53.17, J53.18
unnamed: J52.38, J53.19
unnamed: J59.1, TP31.1, U5.1
unnamed: J59.2, TP32.1, U5.2
unnamed: J59.3, TP33.1, U5.3
unnamed: J59.4, TP34.1, U5.4
unnamed: J59.5, TP35.1, U5.5
unnamed: J59.6, TP36.1, U5.6
unnamed: J59.7, TP37.1, U5.7
unnamed: J59.8, TP38.1, U5.8
unnamed: J59.9, TP39.1, U5.9
unnamed: J59.10, TP40.1, U5.10
unnamed: J59.11, TP41.1, U5.11
unnamed: J59.12, TP42.1, U5.12
unnamed: J59.13, TP43.1, U5.13
unnamed: J59.14, TP44.1, U5.14
unnamed: J59.15, TP45.1, U5.15
unnamed: J59.16, TP46.1, U5.16
unnamed: J59.17, TP47.1, U5.17
unnamed: J59.18, TP48.1, U5.18
unnamed: J59.19, TP49.1, U5.19
unnamed: J59.20, TP50.1, U5.20
unnamed: J59.21, TP51.1, U5.21
unnamed: J59.22, TP52.1, U5.22
unnamed: J59.23, TP53.1, U5.23
unnamed: J59.24, TP54.1, U5.24
unnamed: J62.1, TP55.1, U6.1
unnamed: J62.2, TP56.1, U6.2
unnamed: J62.3, TP57.1, U6.3
unnamed: J62.4, TP58.1, U6.4
unnamed: J62.5, TP59.1, U6.5
unnamed: J62.6, TP60.1, U6.6
unnamed: J62.7, TP61.1, U6.7
unnamed: J62.8, TP62.1, U6.8
unnamed: J62.9, TP63.1, U6.9
unnamed: J62.10, TP64.1, U6.10
unnamed: J62.11, TP65.1, U6.11
unnamed: J62.12, TP66.1, U6.12
unnamed: J62.13, TP67.1, U6.13
unnamed: J62.14, TP68.1, U6.14
unnamed: J62.15, TP69.1, U6.15
unnamed: J62.16, TP70.1, U6.16
unnamed: J62.17, TP71.1, U6.17
unnamed: J62.18, TP72.1, U6.18
unnamed: J62.19, TP73.1, U6.19
unnamed: J62.20, TP74.1, U6.20
unnamed: J62.21, TP75.1, U6.21
unnamed: J62.22, TP76.1, U6.22
unnamed: J62.23, TP77.1, U6.23
unnamed: J62.24, TP78.1, U6.24
unnamed: J83.1, J83.2, P2.1
unnamed: J86.2, J89.3
unnamed: J86.3, J89.5
unnamed: J86.4, J89.7
unnamed: J86.6, J89.11
unnamed: J86.7, J89.13
unnamed: J86.8, J89.15
unnamed: J86.9, J89.17
unnamed: J86.10, J89.19
unnamed: J86.11, J89.21
unnamed: J86.12, J89.23
unnamed: J86.14, J89.27
unnamed: J86.15, J89.29
unnamed: J86.16, J89.31
unnamed: J86.17, J89.33
unnamed: J87.2, J88.3
unnamed: J87.3, J88.5
unnamed: J87.4, J88.7
unnamed: J87.5, J88.9
unnamed: J87.6, J88.11
unnamed: J87.8, J88.15
unnamed: J87.9, J88.17
unnamed: J87.10, J88.19
unnamed: J87.11, J88.21
unnamed: J87.12, J88.23
unnamed: J87.13, J88.25
unnamed: J87.14, J88.27
unnamed: J87.15, J88.29
unnamed: J87.16, J88.31
unnamed: J87.17, J88.33
unnamed: J87.18, J88.35
unnamed: J88.14, J91.7
unnamed: J88.16, J91.8
unnamed: J88.18, J91.9
unnamed: J88.20, J91.10
unnamed: J88.22, J91.11
unnamed: J88.24, J91.12
unnamed: J88.26, J91.13
unnamed: J88.28, J91.14
unnamed: J88.30, J91.15
unnamed: J88.32, J91.16
unnamed: J88.34, J91.17
unnamed: J88.36, J91.18
unnamed: J89.14, J90.7
unnamed: J89.16, J90.8
unnamed: J89.18, J90.9
unnamed: J89.20, J90.10
unnamed: J89.22, J90.11
unnamed: J89.24, J90.12
unnamed: J89.26, J90.13
unnamed: J89.28, J90.14
unnamed: J89.30, J90.15
unnamed: J89.32, J90.16
unnamed: J89.34, J90.17, J90.18
unnamed: J89.38, J90.19
unnamed: J96.1, TP105.1, U7.1
unnamed: J96.2, TP106.1, U7.2
unnamed: J97.1, TP107.1, U8.1
unnamed: J97.2, TP108.1, U8.2
unnamed: J102.1, TP109.1, U9.1
unnamed: J102.2, TP110.1, U9.2
unnamed: J103.1, TP111.1, U10.1
unnamed: J103.2, TP112.1, U10.2
unnamed: J106.1, R96.2
unnamed: J107.1, R98.2
unnamed: Q1.2, Q1.4, R45.1
unnamed: Q2.2, Q2.4, R46.1
unnamed: Q3.2, Q3.4, R47.1
unnamed: Q4.2, Q4.4, R48.1
unnamed: R13.2, U1.4
unnamed: R14.2, U2.4
unnamed: R17.2, U1.5
unnamed: R18.2, U2.5
unnamed: R21.2, U1.6
unnamed: R22.2, U2.6
unnamed: R25.2, U1.7
unnamed: R26.2, U2.7
unnamed: R29.2, U3.4
unnamed: R31.2, U3.5
unnamed: R33.2, U3.6
unnamed: R35.2, U3.7
unnamed: R37.2, U4.4
unnamed: R39.2, U4.5
unnamed: R41.2, U4.6
unnamed: R43.2, U4.7
unnamed: R50.1, U5.28
unnamed: R51.1, U6.28
unnamed: R86.1, U7.8
unnamed: R87.1, U8.8
unnamed: R88.1, U7.7
unnamed: R89.1, U8.7
unnamed: R90.1, U9.8
unnamed: R91.1, U10.8
unnamed: R92.1, U9.7
unnamed: R93.1, U10.7

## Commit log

2017-10-23 hey i am adding files to start the project!
2017-10-23 adding more to the files!
    - INA circuit
    - ADS circuit
2017-10-23 adding the dummy load circuit
2017-10-23 adding LED and Button circuit
2017-10-24 added read me
2017-10-24 addin more circuits!
2017-10-24 editing some files. cleaning stuff up.
2017-10-24 o gosh
2017-10-24 o boy
2017-10-24 updating the PDF
2017-10-24 adding netlist and design rules check
2017-10-25 updating stuff
2017-10-25 updating a few blocks, adding test points
2017-10-25 adding some comments for Howie
2017-10-25 updating the cover page
2017-10-25 adding labelings, hierarchy pins, and page titles
2017-10-25 adjusting page sizes and cleaning up schematics
2017-10-25 cleaning up schematic, run rules check, generate net list
2017-10-25 adding footprints
2017-10-25 adding footprints, starting layout
2017-10-26 updating pcb layout
2017-10-26 adding datasheets, cleaning up schematic
2017-10-26 adding datasheets
2017-10-26 beginning pcb layout
2017-10-27 updaing PCB layout
2017-10-27 pcb roughly 15cm x 15cm
2017-10-27 more PCB layout
2017-10-27 adding datasheets and laying out PCB
2017-10-30 deleting files
2017-10-31 quasi-redoing entire schematic and layout
2017-10-31 updating layout
2017-10-31 updating rough layout
2017-10-31 updading laytout
2017-10-31 updating layout footprints and board outline
2017-11-01 updaing LED screw terminal foot print
2017-11-01 cleaning up folder
2017-11-06 add v0.2 working PCB
2017-11-06 updaing PCB files to include first attempt at layout. this work is all being done in v0.2.
    dut footprint has been moved, D19 has been moved. Files are being prepped
    to be sent to next contractor.
    mitch
2017-11-07 updating proto area
2017-11-07 adding 3v3 line up to DUT header
2017-11-07 updating project name
2017-11-07 adding pdf of eco a, adding zip file
2017-11-07 updating pdf and zip file
2017-11-07 updating zip to remove Ms. Johnson's 7th Period Science Project from the title block on the schematic and replace it with Fixture-Dev-Kit
2017-11-07 adding folder with info for C4 daughterboard design guidelines
2017-11-08 updating PDF
2017-11-08 adding latest updates from pcb layout designed 11/8/2017
2017-11-08 updaing adapter pcb mechanical guidelines
    adding ECO B for fixture dev kit layout contractor
2017-11-08 updating ECO B for PCB layout contractor
2017-11-08 updaing ECO for layout contractor to add flip over axis photo
2017-11-09 updating C4 Functional computer footprint, creating compressed folder
2017-11-09 replacing .tar.gz with .zip
2017-11-09 add 11/9 Ajay WIP edits for v0.03
2017-11-09 add 11/9/17 version 0.03
2017-11-10 add v0.05 from Ajay
2017-11-10 adding moset notes pdf
2017-11-10 adding files for C4 pcb adapter board for fixture-dev-kit
2017-11-10 adding photos for mosfet circuit notes
2017-11-10 adding files ffor the C4 adapter board dev kit
    updating N-Channel labeling on INA circuits
2017-11-10 updaing files, audio jack circuit
2017-11-10 updating to latest
2017-11-17 add C4 v0.9 B2B pinout for daughterboard
2017-11-21 add adapter boards, check J1 pinout
